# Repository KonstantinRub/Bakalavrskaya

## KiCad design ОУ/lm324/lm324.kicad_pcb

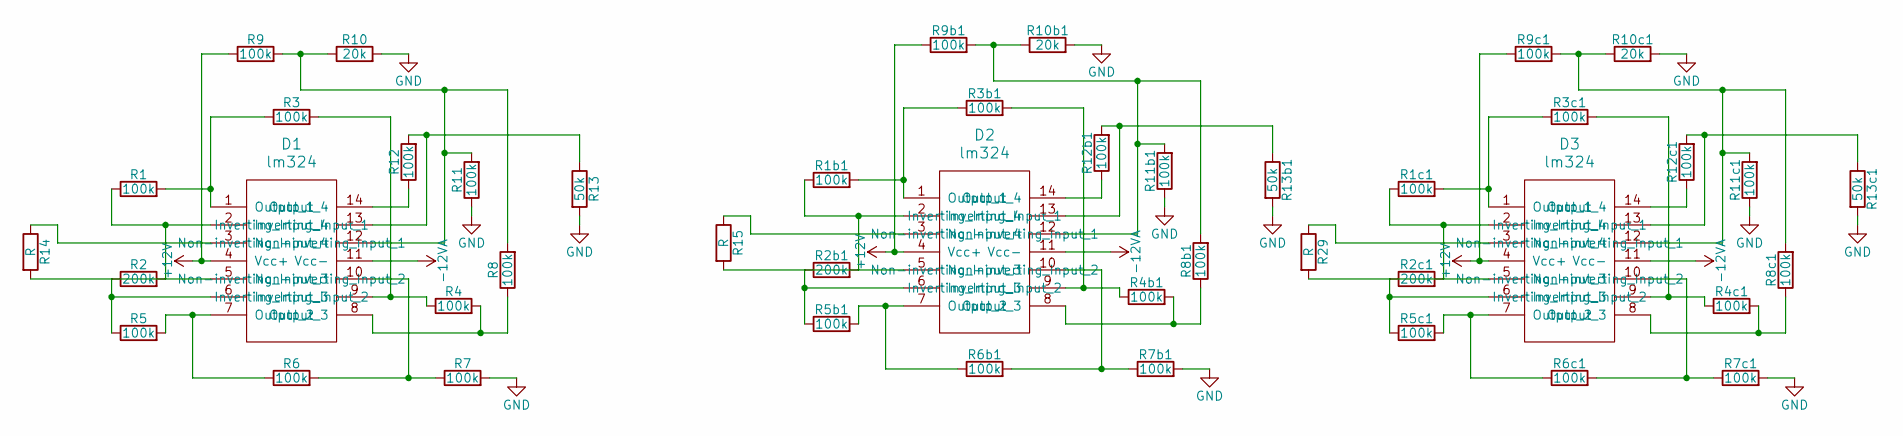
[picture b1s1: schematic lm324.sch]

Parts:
D1, D2, D3: lm324; SW_DIP_x7_Slide
R1, R1b1, R1c1, R3, R3b1, R3c1, R4, R4b1, R4c1, R5, R5b1, R5c1, R6, R6b1, R6c1, R7, R7b1, R7c1, R8, R8b1, R8c1, R9, R9b1, R9c1, R11, R11b1, R11c1, R12, R12b1, R12c1: 100k; Resistor_Horizontal_RM15mm
R2, R2b1, R2c1: 200k; Resistor_Horizontal_RM15mm
R10, R10b1, R10c1: 20k; Resistor_Horizontal_RM15mm
R13, R13b1, R13c1: 50k; Resistor_Horizontal_RM15mm
R14, R15, R29: R; TerminalBlock_WAGO-236_2Stift_RM5mm_2pol

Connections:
+12V: D1.4 (Vcc+), D2.4 (Vcc+), D3.4 (Vcc+), R9.1, R9b1.1, R9c1.1
-12VA: D1.11 (Vcc-), D2.11 (Vcc-), D3.11 (Vcc-)
GND: R7.2, R7b1.2, R7c1.2, R10.2, R10b1.2, R10c1.2, R11.1, R11b1.1, R11c1.1, R13.2, R13b1.2, R13c1.2
unnamed: D1.1 (Output_1), R1.2, R3.1
unnamed: D1.2 (Inverting_Input_1), R1.1, R2.2
unnamed: D1.3 (Non-inverting_Input_1), R14.1
unnamed: D1.5 (Non-inverting_Input_2), R14.2
unnamed: D1.6 (Inverting_Input_2), R2.1, R5.1
unnamed: D1.7 (Output_2), R5.2, R6.1
unnamed: D1.8 (Output_3), R4.2, R8.1
unnamed: D1.9 (Inverting_Input_3), R3.2, R4.1
unnamed: D1.10 (Non-inverting_Input_3), R6.2, R7.1
unnamed: D1.12 (Non-inverting_Input_4), R8.2, R9.2, R10.1, R11.2
unnamed: D1.13 (Inverting_Input_4), R12.2, R13.1
unnamed: D1.14 (Output_4), R12.1
unnamed: D2.1 (Output_1), R1b1.2, R3b1.1
unnamed: D2.2 (Inverting_Input_1), R1b1.1, R2b1.2
unnamed: D2.3 (Non-inverting_Input_1), R15.1
unnamed: D2.5 (Non-inverting_Input_2), R15.2
unnamed: D2.6 (Inverting_Input_2), R2b1.1, R5b1.1
unnamed: D2.7 (Output_2), R5b1.2, R6b1.1
unnamed: D2.8 (Output_3), R4b1.2, R8b1.1
unnamed: D2.9 (Inverting_Input_3), R3b1.2, R4b1.1
unnamed: D2.10 (Non-inverting_Input_3), R6b1.2, R7b1.1
unnamed: D2.12 (Non-inverting_Input_4), R8b1.2, R9b1.2, R10b1.1, R11b1.2
unnamed: D2.13 (Inverting_Input_4), R12b1.2, R13b1.1
unnamed: D2.14 (Output_4), R12b1.1
unnamed: D3.1 (Output_1), R1c1.2, R3c1.1
unnamed: D3.2 (Inverting_Input_1), R1c1.1, R2c1.2
unnamed: D3.3 (Non-inverting_Input_1), R29.1
unnamed: D3.5 (Non-inverting_Input_2), R29.2
unnamed: D3.6 (Inverting_Input_2), R2c1.1, R5c1.1
unnamed: D3.7 (Output_2), R5c1.2, R6c1.1
unnamed: D3.8 (Output_3), R4c1.2, R8c1.1
unnamed: D3.9 (Inverting_Input_3), R3c1.2, R4c1.1
unnamed: D3.10 (Non-inverting_Input_3), R6c1.2, R7c1.1
unnamed: D3.12 (Non-inverting_Input_4), R8c1.2, R9c1.2, R10c1.1, R11c1.2
unnamed: D3.13 (Inverting_Input_4), R12c1.2, R13c1.1
unnamed: D3.14 (Output_4), R12c1.1

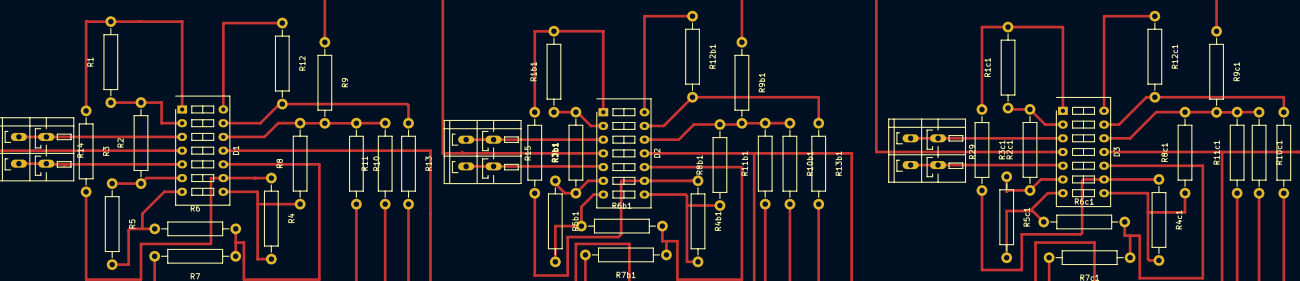
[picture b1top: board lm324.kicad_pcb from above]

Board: 2 copper layers, 45 parts (0 on the bottom side), 39 nets.

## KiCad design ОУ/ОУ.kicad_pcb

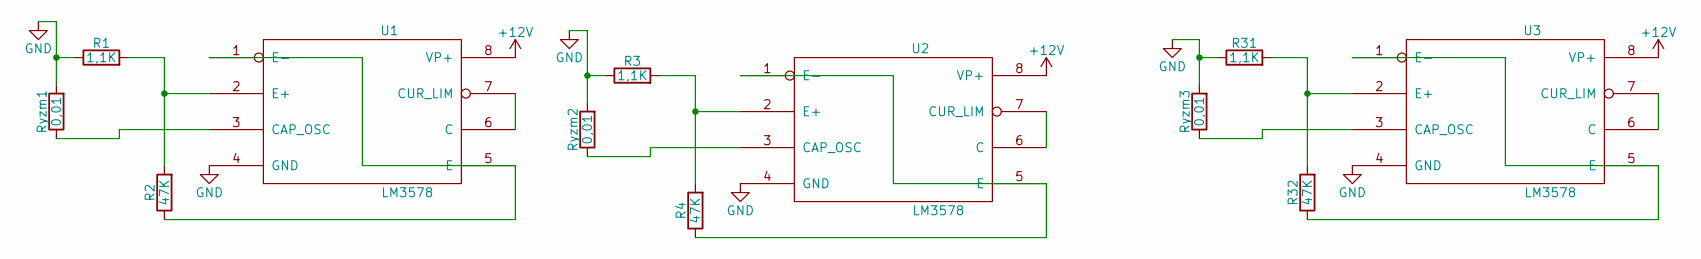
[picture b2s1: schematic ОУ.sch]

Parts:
R1, R3, R31: 1,1К; Resistor_Horizontal_RM10mm
R2, R4, R32: 47К; Resistor_Horizontal_RM10mm
Ryzm1, Ryzm2, Ryzm3: 0,01; Resistor_Horizontal_RM10mm
U1, U2, U3: LM3578; DIP-8_SMD

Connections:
+12V: U1.8 (VP+), U2.8 (VP+), U3.8 (VP+)
GND: R1.1, R3.1, R31.1, Ryzm1.2, Ryzm2.2, Ryzm3.2, U1.4 (GND), U2.4 (GND), U3.4 (GND)
unnamed: R1.2, R2.2, U1.2 (E+)
unnamed: R2.1, U1.1 (E-), U1.5 (E)
unnamed: R3.2, R4.2, U2.2 (E+)
unnamed: R4.1, U2.1 (E-), U2.5 (E)
unnamed: R31.2, R32.2, U3.2 (E+)
unnamed: R32.1, U3.1 (E-), U3.5 (E)
unnamed: Ryzm1.1, U1.3 (CAP_OSC)
unnamed: Ryzm2.1, U2.3 (CAP_OSC)
unnamed: Ryzm3.1, U3.3 (CAP_OSC)
unnamed: U1.6 (C), U1.7 (CUR_LIM)
unnamed: U2.6 (C), U2.7 (CUR_LIM)
unnamed: U3.6 (C), U3.7 (CUR_LIM)

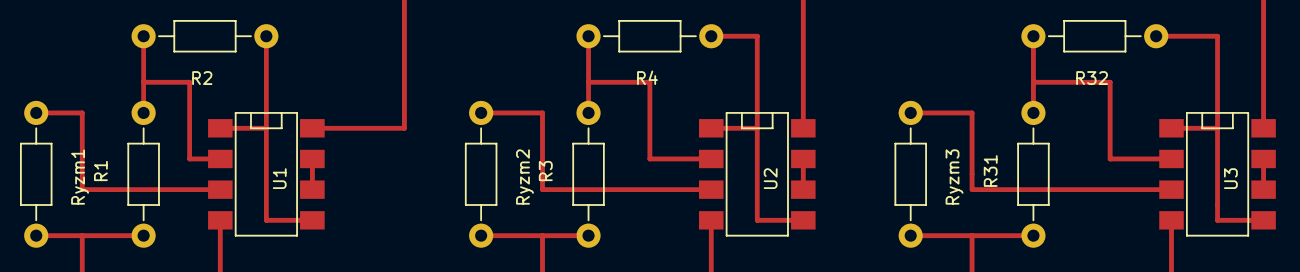
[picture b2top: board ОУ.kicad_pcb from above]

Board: 2 copper layers, 12 parts (0 on the bottom side), 14 nets.

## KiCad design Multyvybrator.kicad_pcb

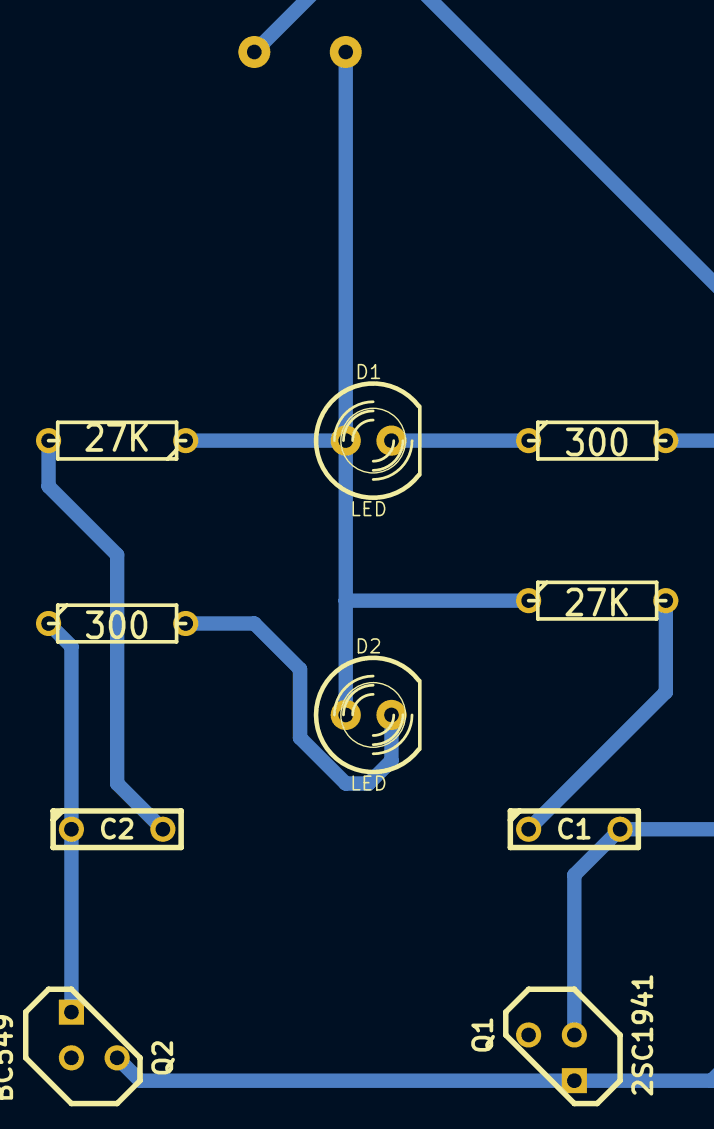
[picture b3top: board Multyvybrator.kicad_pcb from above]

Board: 2 copper layers, 11 parts (1 on the bottom side), 8 nets.

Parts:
BT1: BATTERY; HC-18UH
C1, C2: 47; C2
D1, D2: LED; LED-5MM
Q1: 2SC1941; TO92
Q2: BC549; TO92
R1, R4: 300; R3
R2, R3: 27K; R3

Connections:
unnamed: C2.1, Q2.1, R4.1
unnamed: D2.2, R4.2
unnamed: BT1.1, D1.1, D2.1, R2.1, R3.1
unnamed: D1.2, R1.1
unnamed: C1.2, Q1.2, R1.2
unnamed: C2.2, Q1.3, R3.2
unnamed: C1.1, Q2.2, R2.2
unnamed: BT1.2, Q1.1, Q2.3

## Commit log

2015-11-01 :tada: Added .gitattributes
2015-11-05 Probnaya chast
2015-11-07 Kursovaya
2016-02-09 nachaloone
2016-02-09 nachalo s izmeneniem
2016-02-10 v1.1
2016-02-10 v1.2
2016-02-10 v1.5
2016-02-10 v1.6
2016-02-11 v2.1
2016-02-11 novaya proba
2016-02-11 v3.1
2016-02-11 v3.2
2016-02-11 v3.3
2016-02-15 v3.6
2016-02-15 v3.7
2016-02-15 v4.0
2016-02-15 v4.1
2016-05-11 shema
2016-06-08 diplom
2016-06-09 Diplom 1.1
2016-06-09 Diplom 1.2
2016-06-09 Diplom 1.3
2016-06-09 Diplom 1.4
2016-06-10 Diplom 1.5
2016-06-11 Diplom 1.6
2016-06-17 Diplom 1.7
